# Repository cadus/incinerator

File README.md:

# Firmware & electronics for the CADUS incinerator

Furnace for the incineration of medical waste.

[![PlatformIO CI][]][1]

  [PlatformIO CI]: https://github.com/cadus/incinerator/workflows/PlatformIO%20CI/badge.svg
  [1]: https://github.com/cadus/incinerator/actions?query=workflow%3A%22PlatformIO+CI%22

## [Project documentation on GitHub pages]

  [Project documentation on GitHub pages]: https://cadus.github.io/incinerator/

**Under construction / Work in progress**

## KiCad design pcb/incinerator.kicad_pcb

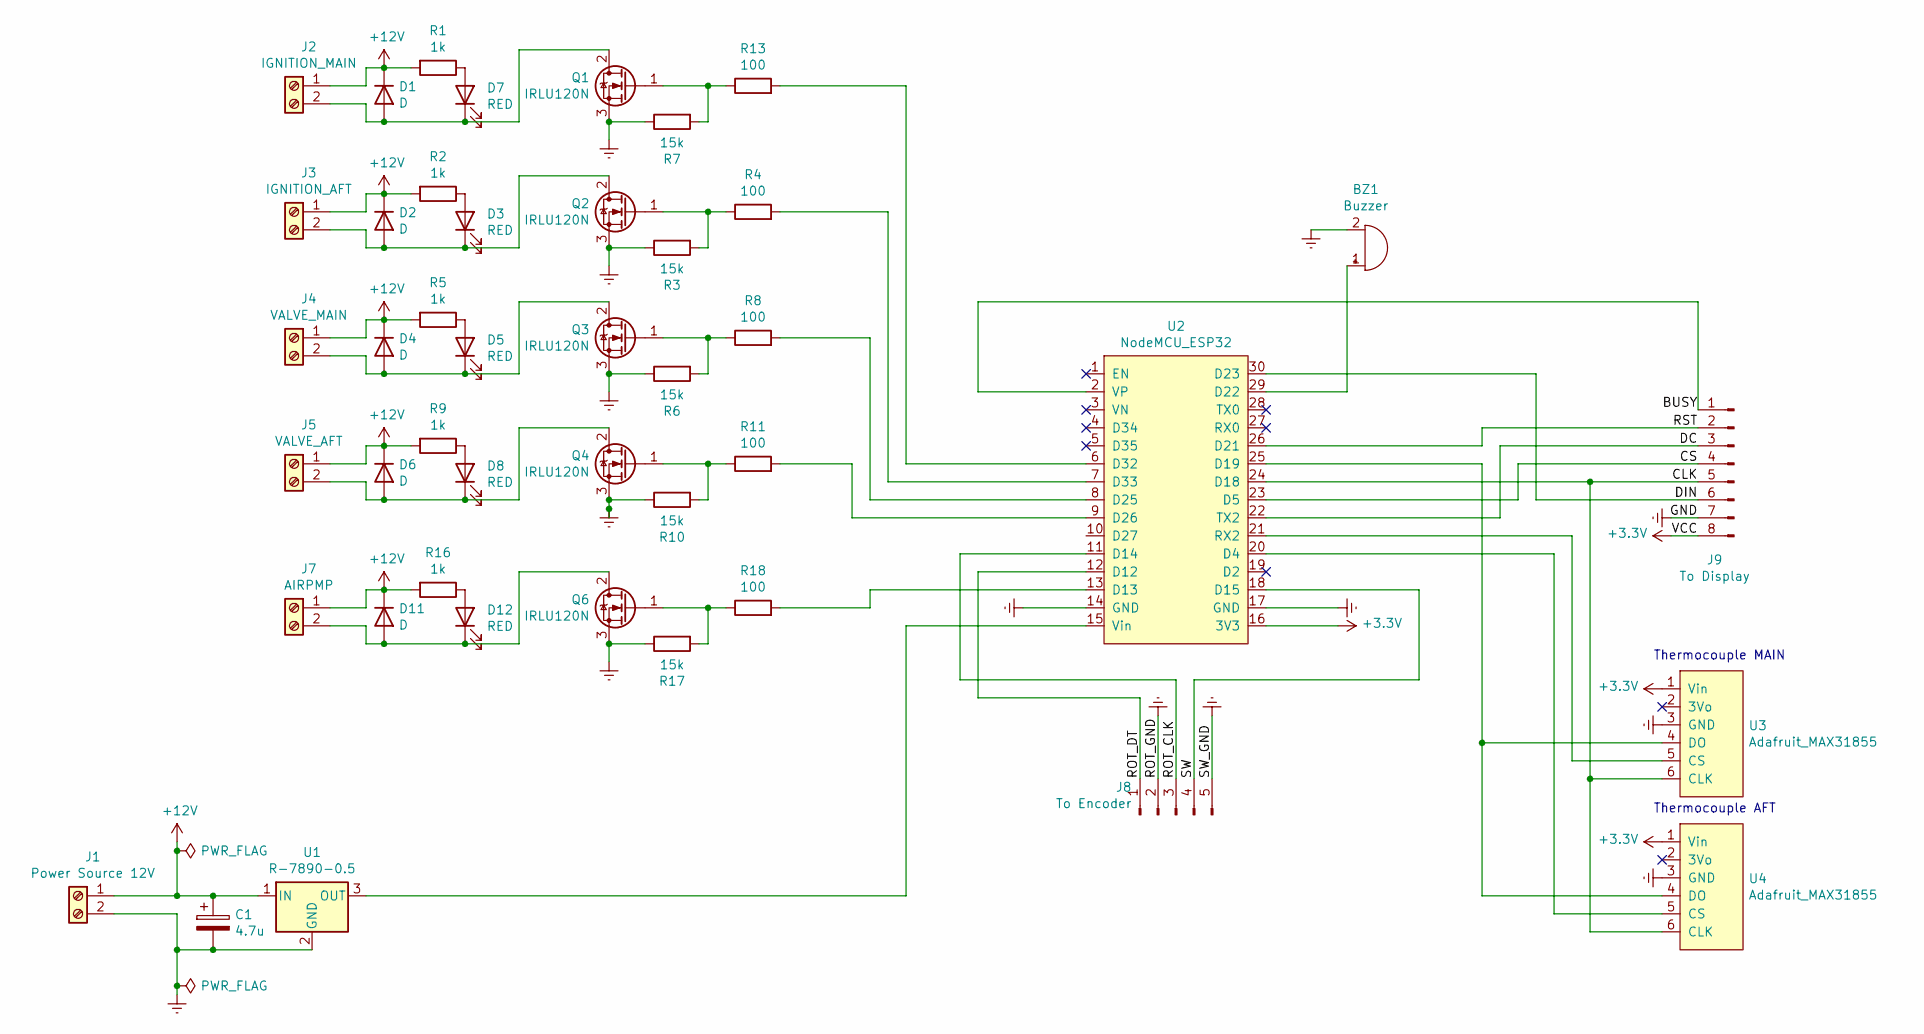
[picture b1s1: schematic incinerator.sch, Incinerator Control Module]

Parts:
BZ1: Buzzer; Buzzer_TDK_PS1240P02BT_D12.2mm_H6.5mm
C1: 4.7u; CP_Radial_D5.0mm_P2.50mm
D1, D2, D4, D6, D11: D; D_DO-41_P7.62mm_Custom
D3, D5, D7, D8, D12: RED; LED_D3.0mm_Custom
J1: Power Source 12V; TerminalBlock_bornier-2_P5.08mm
J2: IGNITION_MAIN; TerminalBlock_bornier-2_P5.08mm
J3: IGNITION_AFT; TerminalBlock_bornier-2_P5.08mm
J4: VALVE_MAIN; TerminalBlock_bornier-2_P5.08mm
J5: VALVE_AFT; TerminalBlock_bornier-2_P5.08mm
J7: AIRPMP; TerminalBlock_bornier-2_P5.08mm
J8: To Encoder; PinHeader_1x05_P2.54mm_Vertical
J9: To Display; PinHeader_1x08_P2.54mm_Vertical
Q1, Q2, Q3, Q4, Q6: IRLU120N; SIPAK_Vertical_Custom
R1, R2, R5, R9, R16: 1k; R_THT_D2.5mm_P7.62mm_Custom
R3, R6, R7, R10, R17: 15k; R_THT_D2.5mm_P7.62mm_Custom
R4, R8, R11, R13, R18: 100; R_THT_D2.5mm_P7.62mm_Custom
U1: R-7890-0.5; Converter_DCDC_RECOM_R-78E-0.5_THT
U2: NodeMCU_ESP32; ESP32_NodeMCU
U3, U4: Adafruit_MAX31855

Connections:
+3V3: J9.8, U2.16 (3V3), U3.1 (Vin), U4.1 (Vin)
+12V: C1.1, D1.1 (K), D2.1 (K), D4.1 (K), D6.1 (K), D11.1 (K), J1.1, J2.1, J3.1, J4.1, J5.1, J7.1, R1.2, R2.2, R5.2, R9.2, R16.2, U1.1 (IN)
/BUSY: J9.1, U2.2 (VP)
/CLK: J9.5, U2.24 (D18), U3.6 (CLK), U4.6 (CLK)
/CS: J9.4, U2.23 (D5)
/DC: J9.3, U2.22 (TX2)
/DIN: J9.6, U2.30 (D23)
/ROT_CLK: J8.3, U2.11 (D14)
/ROT_DT: J8.1, U2.12 (D12)
/RST: J9.2, U2.26 (D21)
/SW: J8.4, U2.18 (D15)
Earth: BZ1.2 (+), C1.2, J1.2, J8.2, J8.5, J9.7, Q1.3 (S), Q2.3 (S), Q3.3 (S), Q4.3 (S), Q6.3 (S), R3.1, R6.1, R7.1, R10.1, R17.1, U1.2 (GND), U2.14 (GND), U2.17 (GND), U3.3 (GND), U4.3 (GND)
unnamed: BZ1.1 (-), U2.29 (D22)
unnamed: D1.2 (A), D7.1 (K), J2.2, Q1.2 (D)
unnamed: D2.2 (A), D3.1 (K), J3.2, Q2.2 (D)
unnamed: D3.2 (A), R2.1
unnamed: D4.2 (A), D5.1 (K), J4.2, Q3.2 (D)
unnamed: D5.2 (A), R5.1
unnamed: D6.2 (A), D8.1 (K), J5.2, Q4.2 (D)
unnamed: D7.2 (A), R1.1
unnamed: D8.2 (A), R9.1
unnamed: D11.2 (A), D12.1 (K), J7.2, Q6.2 (D)
unnamed: D12.2 (A), R16.1
unnamed: Q1.1 (G), R7.2, R13.1
unnamed: Q2.1 (G), R3.2, R4.1
unnamed: Q3.1 (G), R6.2, R8.1
unnamed: Q4.1 (G), R10.2, R11.1
unnamed: Q6.1 (G), R17.2, R18.1
unnamed: R4.2, U2.7 (D33)
unnamed: R8.2, U2.8 (D25)
unnamed: R11.2, U2.9 (D26)
unnamed: R13.2, U2.6 (D32)
unnamed: R18.2, U2.13 (D13)
unnamed: U1.3 (OUT), U2.15 (Vin)
unnamed: U2.20 (D4), U4.5 (CS)
unnamed: U2.21 (RX2), U3.5 (CS)
unnamed: U2.25 (D19), U3.4 (DO), U4.4 (DO)

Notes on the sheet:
Thermocouple MAIN
Thermocouple AFT

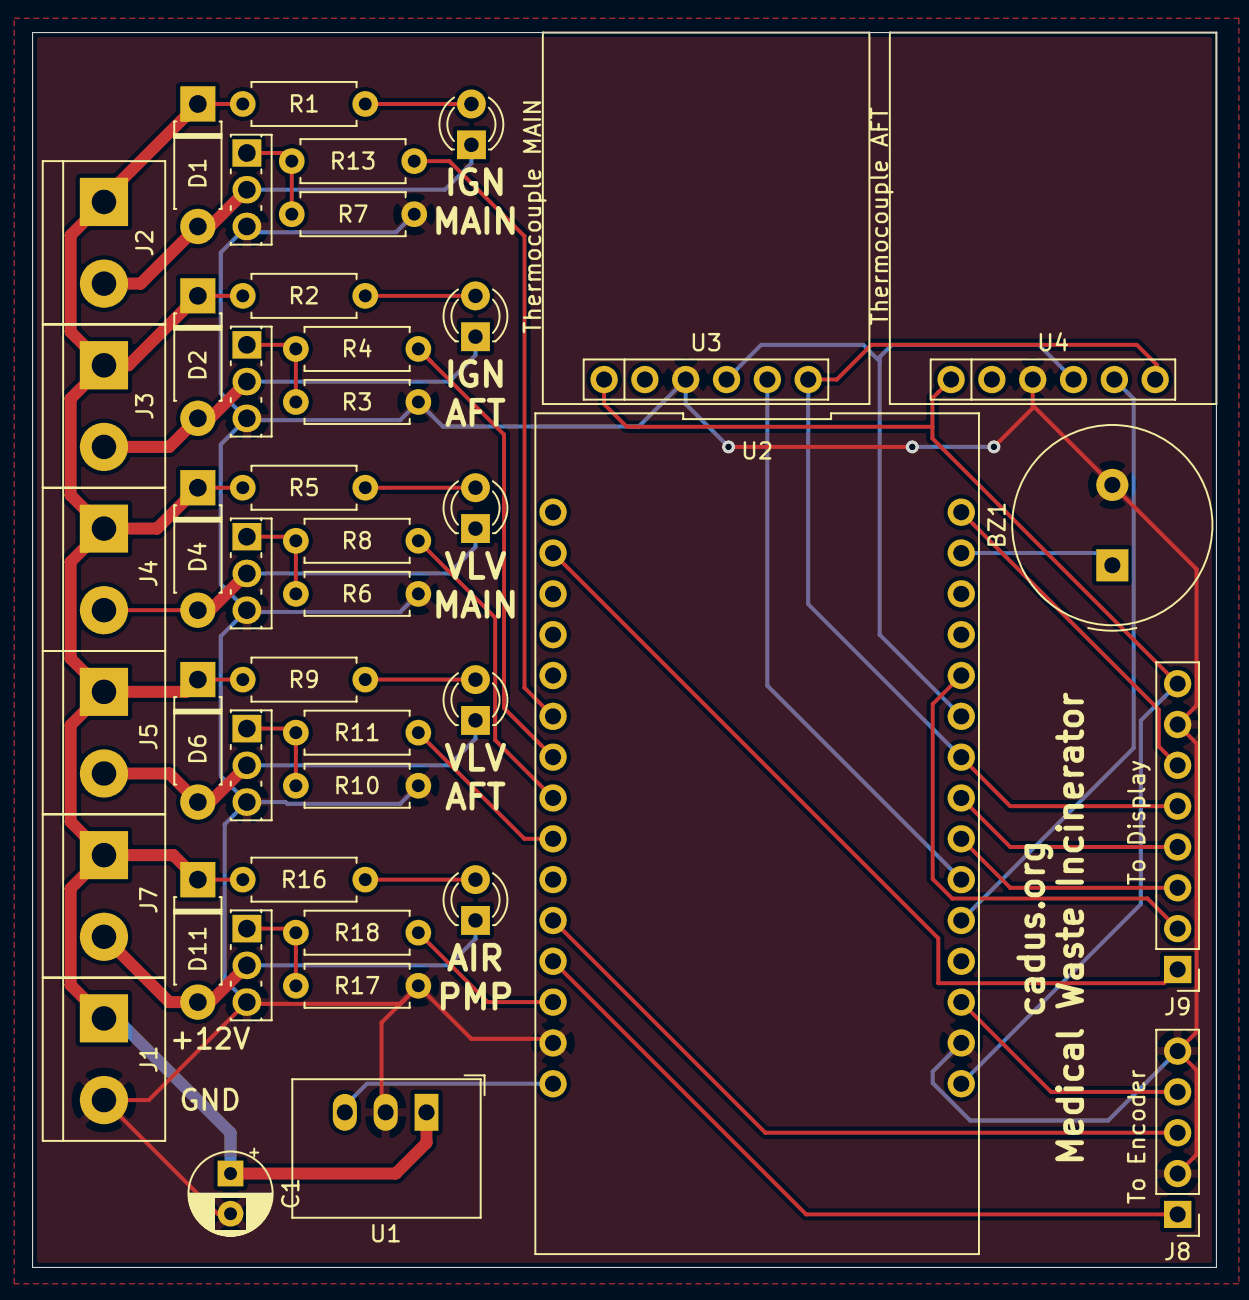
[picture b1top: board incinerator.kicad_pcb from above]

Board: 2 copper layers, 73.7 x 76.8 mm, 44 parts (0 on the bottom side), 37 nets.

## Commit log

2019-11-18 removed former encoder code, added s/w debouncing
2019-11-18 changed to non-blocking
2019-11-18 tried own rotary encoding
2019-11-18 added check_rotary()
2019-11-18 Added support for thermocouple
2019-11-18 increased monitor baudrate
2019-11-18 added hw_config.h
2019-11-18 added support for encoder rotation
2019-11-18 override autodetected usb port
2019-11-18 cleaned up encoder functions and moved to dedicated module
2019-11-18 added Atmel datasheet
2019-11-18 moved MAX cs and added LEDs
2019-11-18 removed encoder_switch_isr() to handle switch in timer isr
2019-11-18 added thermoprobe readout
2019-11-18 Added autoformatter
2019-11-18 initial
2019-11-18 added support for icons
2019-11-18 Moved display-related code to separate module
2019-11-18 Added scriptable graphics conversion from SVG to source code
2019-11-18 created scripts directory
2019-11-18 Show temperature history
2019-11-18 removed uC datasheet from doc folder
2019-11-18 Display thermocouple readout on epaper
2019-11-18 display int. + ext. temp
2019-11-18 Added support for e-paper
2019-11-18 added pinout
2019-11-18 Code format
2019-11-18 Added buzzer support
2019-11-18 Moved thermocouple i/f to separate module
2019-11-18 Changed icon names to upper case
2019-11-18 Generated code consistent with auto-formatter
2019-11-18 Add comment to generated files
2019-11-18 Added support for PNG icons
2019-11-24 Added KiCad schematic
2019-11-24 added ESP32 board schematic
2019-11-24 Add GxEPD2_busyWaitCallback()
2019-11-24 removed hw deps other than epd
2019-11-24 Added encoder value display
2019-11-24 added ESP32 pinout
2019-11-24 Ported display code to ESP32
2019-11-24 Added display benchmarking code
2019-11-24 update display ASAP if something changed
2019-11-24 removed uC datasheets
2019-11-24 Added box icons for "progress bar"
2019-11-24 Added support for int. LED
2019-11-24 re-enable display
2019-11-24 Moved pcb file up one level
2019-11-24 ported icon create script to esp32
2019-11-24 Completed schematic
2019-11-24 adapted to new HW version
2019-11-24 updated libs
2019-11-24 ported icons to esp32
2019-11-24 updated .gitignore
2019-12-04 Changed thermocouple PCB to generic off-brand one
2019-12-06 added buzzer object & removed LED PWM test
2019-12-06 changed thermocouple naming
2019-12-06 wrapped thermocouples into objects
2019-12-06 added support for buzzer volume (duty cycle)
2019-12-06 added led pwm test code
2019-12-06 Added timeout class
2019-12-06 Moved LED_INT to buzzer class
2019-12-06 Added Ignition class
2019-12-06 Timeout elapsed by default
2019-12-06 Added skeleton code for burn chamber & incinerator
2019-12-06 Moved thermocouple instances to incinerator
2019-12-09 added display refresh each second
2019-12-09 removed paged drawing
2019-12-09 improved folder structure
2019-12-09 changed display to class
2019-12-09 added background task
2019-12-09 Added icons
2019-12-09 added option to resize icons to specified height
2019-12-09 first implementation of top bar
2019-12-10 Added macros for disabling copying/moving of classes representing hardware objects
2019-12-10 Renamed display to screen
2019-12-10 Added status bar
2019-12-10 Created dedicated folder for screens
2019-12-10 Added sys config dictionary
2019-12-11 simplified sys_config & added flash code
2019-12-11 made ISR-related code safe to run while flashing
2019-12-11 Add support for buzzer volume config
2019-12-11 Added skeleton code for UI class and conf screen
2019-12-11 moved UI related code to UI class
2019-12-11 Added support for conf items
2019-12-12 first working implementation of conf screen
2019-12-12 Added convenience functions to avoid using getTextBounds() directly
2019-12-12 Done most of the conf screen functionaliry.
2019-12-12 Changed font from mono to sans
2019-12-12 Some eye candy changes
2019-12-12 Removed obsolete AVR section
2019-12-13 Added README
2019-12-13 Protect concurrent access with mutex
2019-12-13 Fixed copy paste bug
2019-12-13 fix build
2019-12-13 consolidated print functions and added bitfield flags
2019-12-13 ISR-safe ledcWrite() for buzzer
2019-12-13 Added missing IRAM_ATTR to timeout increment
2019-12-13 Don't enter value mode when user hits 'Apply'
2019-12-14 Added generic framework for interactive screens
2019-12-14 Added ValueEntry class
2019-12-14 added testscreens
2019-12-14 Added push button handler callback
2019-12-14 Added functionality to navigate between screens
2019-12-14 Added ScreenChangeButton
2019-12-14 adapted ConfScreen to use the InteractiveScreen / InteractiveItem API
2019-12-14 Don't accept user input when screen is being changed
2019-12-14 Added wraparound option for encoder input
2019-12-14 Make a full refresh, wenn the screen changes
2019-12-14 Removed obsolete full refresh on bootup
2019-12-14 Eye candy for config screen
2019-12-14 Added generic support for help text
2019-12-14 Print burn chamber temperatures in bold
2019-12-14 Added ignition config
2019-12-14 Removed dummy test code
2019-12-14 Print config categories in bold
2019-12-15 Removed backup capacitor (needs proper charging circuit)
2019-12-15 Moved I/O pins due to pin restrictions
2019-12-15 Added air pump
2020-01-03 Added syslog
2020-01-03 Removed PWM test code
2020-01-03 Removed air pump & burn chambers from global namespace
2020-01-03 Explicitly init MAX31855 & catch invalid temp. readings
2020-01-03 Give names to burners / iginitions / thermocouples
2020-01-03 Deactivate refresh time output
2020-01-03 Added AirPump::isOn()
2020-01-03 Added option to draw push button w/o enclosing rect
2020-01-03 Added test screen
2020-01-03 fix include directory for code style script
2020-01-04 Make auto generated icon list consistent with clang-format
2020-01-04 Use clang-format instead of astyle for autoformatting
2020-01-04 clang-format: Align after open bracket
2020-01-04 Make icon table generation consistent with autoformatting
2020-01-04 Add stubs for mkdocs
2020-01-04 Ignore mkdocs-generated website
2020-01-04 Add script to deploy docs
2020-01-04 Added docs link in readme
2020-01-04 Move information from README to mkdocs
2020-01-04 Replaced test page with actual content
2020-01-04 Generate version information from build script
2020-01-05 Add low side MOSFETs for furnace control
2020-01-05 Include schematic as SVG in mkdocs page
2020-01-05 Update DCDC info & added support capacitor
2020-01-06 Added project-specific KiCad library for breakout boards
2020-01-06 Renamed furnace control signals for better clarity
2020-01-06 Use mermaid state diagram for state machine
2020-01-07 Added KiCad symbol for thermocouple breakout board
2020-01-07 Add author & license info to schematic
2020-01-07 Added ctrl leds to furnace terminals
2020-01-07 reassigned symbols
2020-01-07 Update schematic in docs
2020-01-07 Add documentation for incinerator & burn chamber
2020-01-08 Add support for Alps encoder
2020-01-10 Add power flags to satisfy KiCad electrical rule check
2020-01-10 Fix symbol for thermocouple breakout board & added N/C marks to satisfy electrical rule check
2020-01-10 Add connector to interface the encoder/switch
2020-01-10 Re-annotated symbols
2020-01-10 Added custom footprints
2020-01-10 Assigned footprints
2020-01-10 started layout (WIP)
2020-01-10 First draft of PCB layout
2020-01-10 Fix markdown table formatting
2020-01-10 Updated schematic in docs
2020-01-11 Added GPLv3 license & added license headers to source files.
2020-01-11 removed breadboard traces from pcb
2020-01-11 reduced THT footprints from 10.16 to 7.62mm
2020-01-12 re-worked & shrinked PCB
2020-01-12 Added WIP note to readme
2020-01-16 Add PCB infos
2020-01-16 aligned track width/clearance w/ smartprototyping.com & added settings for power tracks
2020-01-16 increased pad sizes for breakout boards
2020-01-16 updated pad sizes in PCB
2020-01-16 added traces & ground planes
2020-01-16 Created gerber / drill files
2020-01-25 Added comments
2020-01-27 Swapped encoder clock & data pins
2020-01-27 Increased drill sizes for breakout boards, so they can be mounted directly
2020-01-27 Added Open Source Hardware logo
2020-01-27 Added photo to README
2020-02-03 Refactored power switch channels to KiCad sub-sheet
2020-06-02 Deployed a7a99f7 with MkDocs version: 1.1.2
2020-06-02 Changed repo URL from private account to org account
2020-12-06 Add missing dependencies
2020-12-06 Make ignition & thermocouple public
2020-12-06 Add ignition::getModeStr()
2020-12-06 Add IgnMainTest button
2020-12-07 Add ignition test buttons for both ignitions
2020-12-07 Re-work ignition module to match the state machine in doc
2020-12-08 Fix pinout
2020-12-08 Add valves to burn chamber
2020-12-08 Add valve test buttons to test screen
2020-12-08 Start up with test screen
2020-12-21 Add more icons
2020-12-23 Add Icon class
2020-12-23 Auto-crop icons & add snowflake
2020-12-24 Add GitHub workflow
2020-12-24 CI: force-fetch tags
2020-12-24 Improve const correctness
2020-12-24 Add skeleton for BurnChamber state machine
2020-12-25 Improve naming
2020-12-25 Add home screen
2020-12-25 Further improve naming
2020-12-25 Add burn chamber state machine
2020-12-25 Rearrange test screen, make room for burner test buttons
2020-12-26 Add firmware update instructions
2020-12-26 Make burn chambers / air pump public
2020-12-26 Add serial_ctrl and option for temperature simulation
2020-12-26 Add 'temperature simulation' tool
2020-12-26 Deployed 6ac0177 with MkDocs version: 0.16.3
2020-12-26 Deployed 6ac0177 with MkDocs version: 1.1.2
2020-12-26 Upgrade docs to use mkdocs-mermaid2-plugin
2020-12-26 Deployed 275d0f8 with MkDocs version: 1.1.2
2020-12-26 Add burn chamber test buttons
2020-12-26 Add waitBurnHigh state to check re-ignition at lower end of temperature range
2020-12-26 Deployed a41bec4 with MkDocs version: 1.1.2
2020-12-26 Fix help text
2020-12-26 Add state machine for incinerator
2020-12-29 Speed up upload to ESP
2020-12-29 Add incinerator test button
2020-12-29 Show help text only on item change (avoid log messages being hidden by help text)
2020-12-29 Add info messages for incineration process
2020-12-29 Add progress for incineration
2020-12-29 Add config for cool temp. & burn time
2020-12-29 Add cooldown mode
2020-12-30 Build regular firmware.bin and copy to versioned bin file
2020-12-30 Fix pre- & post-build scripting
2020-12-30 Add flasher
2020-12-30 Rename updater to flasher, create flasher artifact in post-build action
2020-12-30 Add flasher instructions for Windows
2021-01-01 Add support for custom_config.ini
2021-01-01 Refresh help text on new screen
2021-01-01 Add start screen
2021-01-01 Add time entry screen
2021-01-04 Add support for screenshots
2021-01-04 Move flasher instructions to main documentation
2021-01-04 Add documentation for serial control
2021-01-04 Auto-crop big icons
2021-01-04 Add confirmation screen & burn screen
2021-01-04 Add incinerator::abort() and dedicated cooldown modes for abort & failure
2021-01-04 Deployed beb1a29 with MkDocs version: 1.1.2
2021-01-05 Add dedicated 'aborted' mode
2021-01-05 Add cooldown screen
2021-01-05 Add failure screen
2021-01-05 Fixed UI states
2021-01-05 Add screenshots to documentation
2021-01-05 Deployed 28bf910 with MkDocs version: 1.1.2
2021-02-20 Add encoder wiring information
2021-02-20 Deployed c597699 with MkDocs version: 1.1.2
2021-04-21 Fix link error w/ recent arduinoespressif32 framework
2021-04-21 Start port to TFT
2021-05-04 Revert schematic to earlier version to keep connection to PCB footprints
    This reverts commit a7a99f7f60577d9f8a86e54cb3c3f2c49a53cb32.
2021-05-04 pcb: Delete AFT.LO channel
    Rearrange screw connectors
2021-05-05 Remove 2nd afterburner valve in code and documentation
2021-05-05 docs: Update PCB SVG
2021-05-05 Deployed e55b918 with MkDocs version: 1.1.2
2021-05-05 Remove 2nd afterburner valve from test screen
2021-06-27 GxEPD2: specify commit hash in dependencies
2021-06-27 flasher: Update to recent esptool API

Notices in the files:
pcb/incinerator.kicad_pcb:
License: CC BY 4.0
pcb/incinerator.sch:
creativecommons.org/licenses/by/4.0
